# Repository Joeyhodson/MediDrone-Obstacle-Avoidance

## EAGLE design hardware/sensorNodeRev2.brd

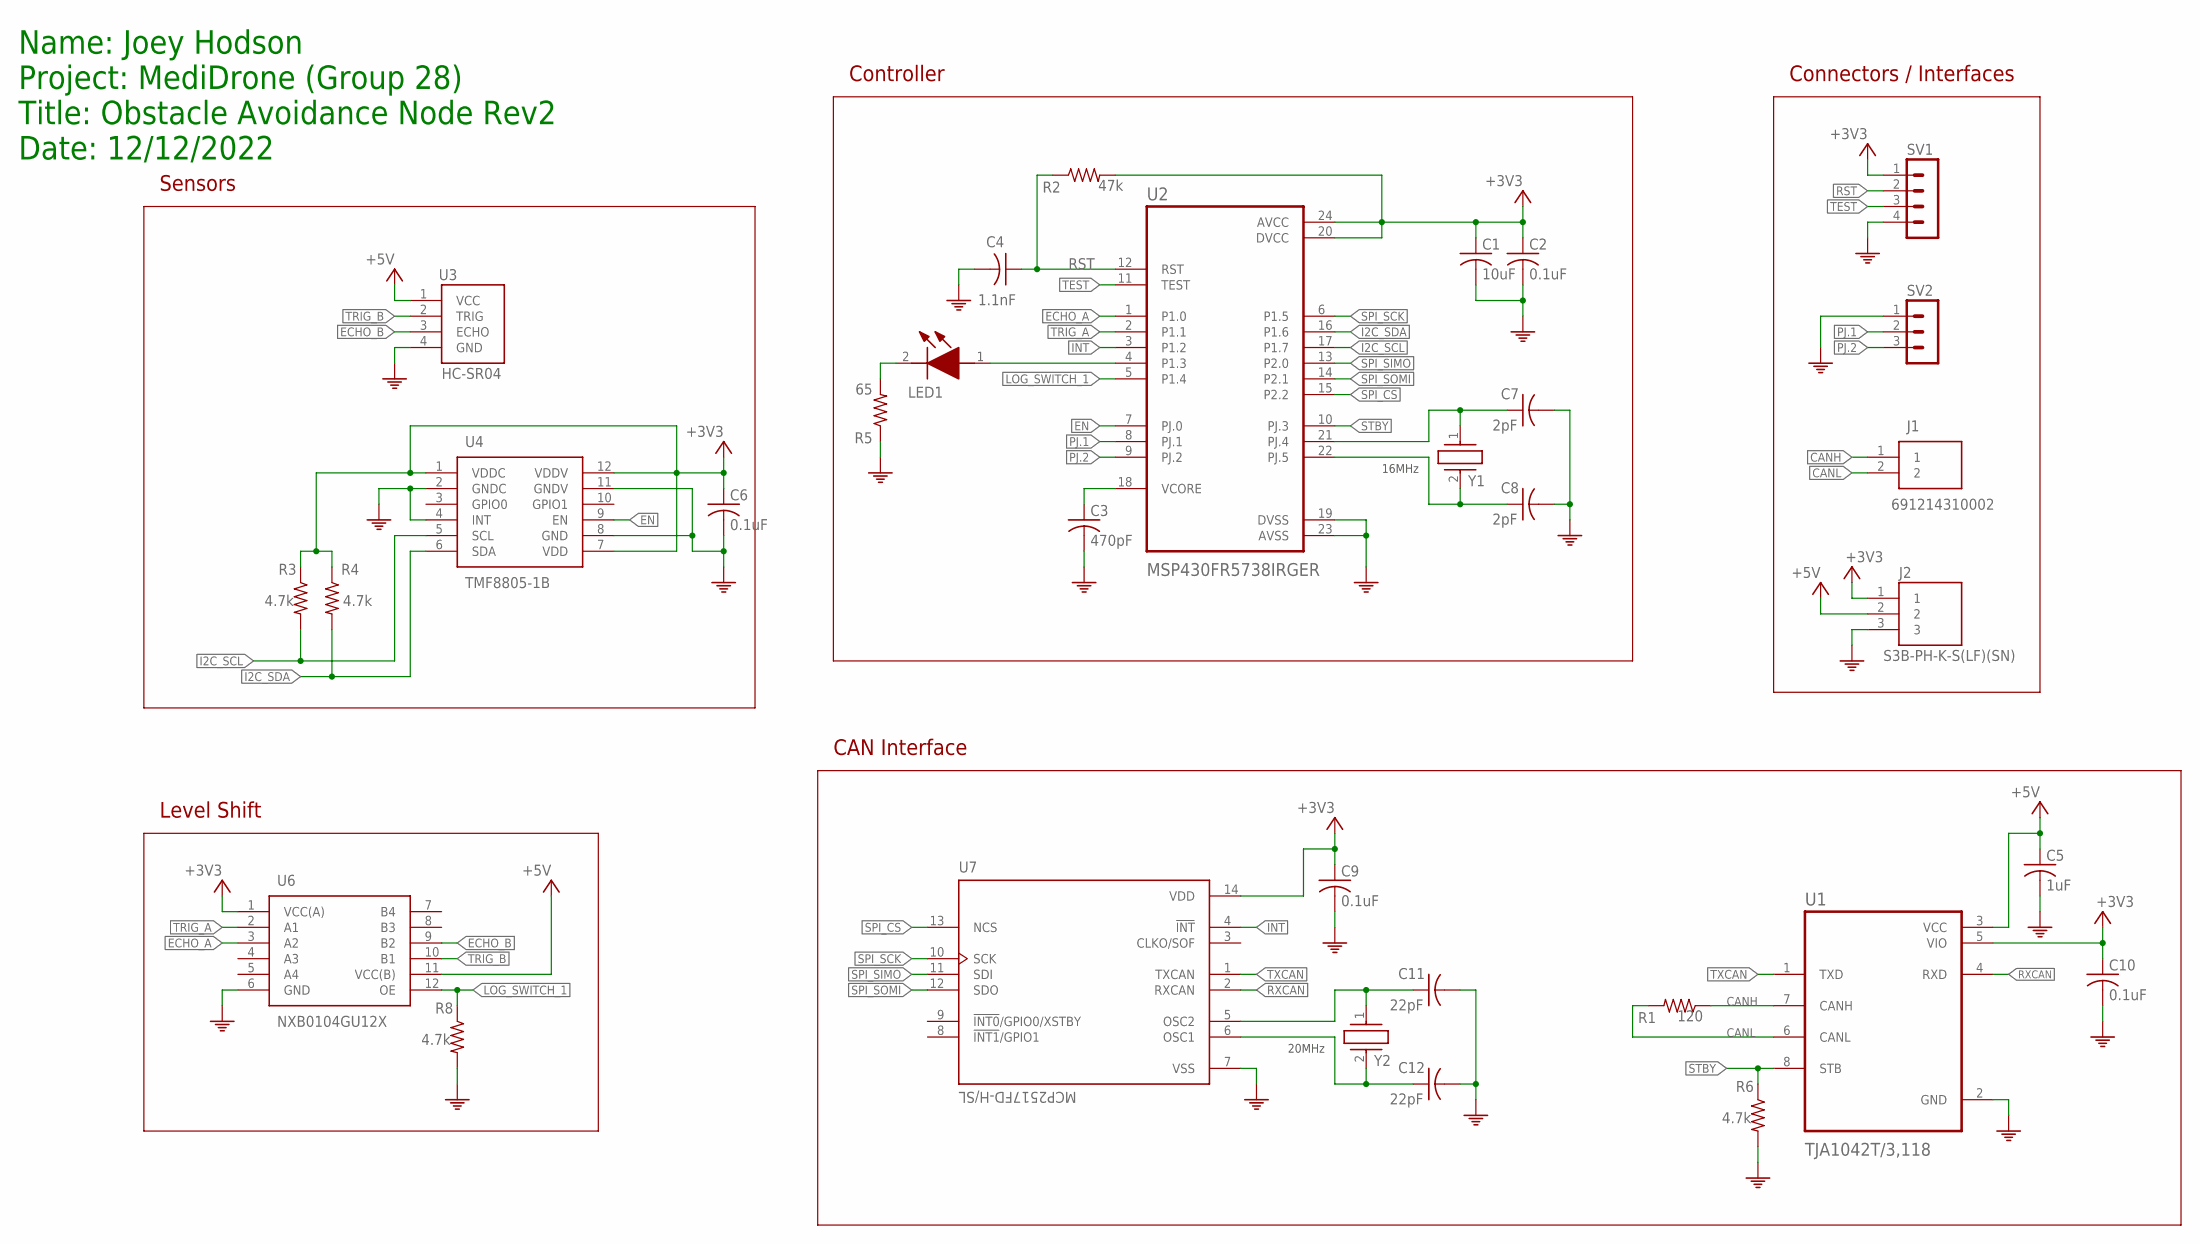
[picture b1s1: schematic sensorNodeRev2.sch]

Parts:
C1: 10uF; C0805
C2, C6, C9, C10: 0.1uF; C0603
C3: 470pF; C0603
C4: 1.1nF; C0603
C5: 1uF; C0603
C7, C8: 2pF; C0603
C11, C12: 22pF; C0603
J1: 691214310002; SHDR2W90P0X381_1X2_802X740X850
J2: S3B-PH-K-S(LF)(SN); JST_S3B-PH-K-S(LF)(SN)
LED1: SML-LX0603IW-TR; SMLLX0603IWTR
R1: 120; R0603
R2: 47k; R0603
R3, R4, R6, R8: 4.7k; R0603
R5: 65; R0603
SV1: MA04-1
SV2: MA03-1
U1: TJA1042T/3,118; SOIC127P600X175-8N
U2: MSP430FR5738IRGER; QFN50P400X400X100-25N
U3: HC-SR04; HC-SR04_VARIANT
U4: TMF8805-1B; TMF88051B
U6: NXB0104GU12X
U7: MCP2517FD-H/SL; SOIC127P600X175-14N
Y1, Y2: HC-49_U-S16000000ABJB; HC49

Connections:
0: C1.2, C2.2, C3.2, C4.2, C5.2, C6.2, C7.2, C8.2, C9.2, C10.2, C11.2, C12.2, J2.3, R5.1, R6.2, R8.2, SV1.4, SV2.1, U1.2 (GND), U2.19 (DVSS), U2.23 (AVSS), U3.4 (GND), U4.2 (GNDC), U4.4 (INT), U4.8 (GND), U4.11 (GNDV), U6.6 (GND), U7.7 (VSS)
+3V3: C1.1, C2.1, C6.1, C9.1, C10.1, J2.1, R2.2, R3.1, R4.1, SV1.1, U1.5 (VIO), U2.20 (DVCC), U2.24 (AVCC), U4.1 (VDDC), U4.7 (VDD), U4.12 (VDDV), U6.1 (VCC(A)), U7.14 (VDD)
+5V: C5.1, J2.2, U1.3 (VCC), U3.1 (VCC), U6.11 (VCC(B))
CANH: J1.1, R1.1, U1.7 (CANH)
CANL: J1.2, R1.2, U1.6 (CANL)
ECHO_A: U2.1 (P1.0), U6.3 (A2)
ECHO_B: U3.3 (ECHO), U6.9 (B2)
EN: U2.7 (PJ.0), U4.9 (EN)
I2C_SCL: R3.2, U2.17 (P1.7), U4.5 (SCL)
I2C_SDA: R4.2, U2.16 (P1.6), U4.6 (SDA)
INT: U2.3 (P1.2), U7.4 (!INT)
LOG_SWITCH_1: R8.1, U2.5 (P1.4), U6.12 (OE)
unnamed: C11.1, U7.5 (OSC2), Y2.1
unnamed: C3.1, U2.18 (VCORE)
unnamed: C12.1, U7.6 (OSC1), Y2.2
unnamed: C7.1, U2.21 (PJ.4), Y1.1
unnamed: C8.1, U2.22 (PJ.5), Y1.2
unnamed: LED1.1 (A), U2.4 (P1.3)
unnamed: LED1.2 (K), R5.2
PJ.1: SV2.2, U2.8 (PJ.1)
PJ.2: SV2.3, U2.9 (PJ.2)
RST: C4.1, R2.1, SV1.2, U2.12 (RST)
RXCAN: U1.4 (RXD), U7.2 (RXCAN)
SPI_CS: U2.15 (P2.2), U7.13 (NCS)
SPI_SCK: U2.6 (P1.5), U7.10 (SCK)
SPI_SIMO: U2.13 (P2.0), U7.11 (SDI)
SPI_SOMI: U2.14 (P2.1), U7.12 (SDO)
STBY: R6.1, U1.8 (STB), U2.10 (PJ.3)
TEST: SV1.3, U2.11 (TEST)
TRIG_A: U2.2 (P1.1), U6.2 (A1)
TRIG_B: U3.2 (TRIG), U6.10 (B1)
TXCAN: U1.1 (TXD), U7.1 (TXCAN)

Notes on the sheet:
Name: Joey Hodson Project: MediDrone (Group 28) Title: Obstacle Avoidance Node Rev2 Date: 12/12/2022
16MHz
20MHz
Controller
Connectors / Interfaces
CAN Interface
Sensors
Level Shift

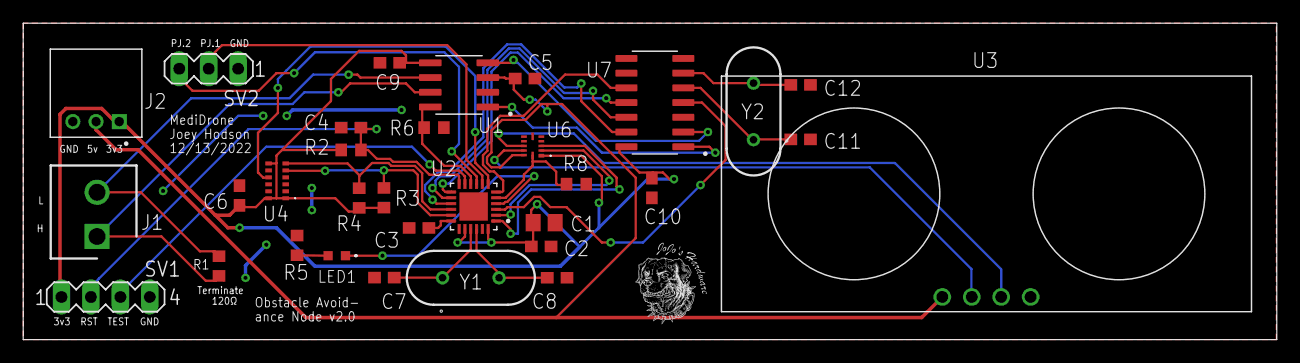
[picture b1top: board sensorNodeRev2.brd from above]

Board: 2 copper layers, 108.1 x 27.3 mm, 32 parts (0 on the bottom side), 32 nets.

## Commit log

2023-01-27 Added schematic, board, and gerber files. EDA - AutoDesk Eagle
2023-01-27 Was able to light LED1 up and stabilize XIN crystal. Clock configuration setup. Attempting to communicate with TMF8805. Plan to utilize MSP430 DriverLib.
2023-01-30 Communication successful with tmf8805. Cleaner code
2023-02-09 added tmf8805 lib
2023-02-22 Successful writes of multiple bytes and reads of one byte with new tof library
2023-02-24 Added bootloader
2023-02-24 Added helper script to convert encrypted image into i2c sequences for ram patch.
2023-02-27 Need to resolve issues with TMF ram patch. Added working configuration of hcsro4 to measure distances greater than 1.5m.
2023-02-27 Update to RAM script
2023-03-05 Added Microchip's MCP251x API, configured SPI transfer underneath interface. TXCAN does is currently not writeable in normal mode or loopback mode; more experimentation required.
2023-03-06 Ultrasonic working on boards 1&2
